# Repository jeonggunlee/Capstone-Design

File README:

[weather Box][raining]
[raining]:https://youtu.be/GDOYBwniNqM

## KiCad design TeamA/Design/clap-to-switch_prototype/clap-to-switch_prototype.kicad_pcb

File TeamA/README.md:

https://github.com/cobaltp/clap-to-switch

Clap-to-Switch Project
Hallym University Capstone Design Project, Spring 2018\
한림대학교 컴퓨터공학과 종합설계프로젝트, 2018년 1학기

Clap-to-Switch Project\
박수 소리로 스위치 작동 프로젝트

목차
==========
1. [개요](#introduction)
1. [알고리즘](#algorithm)
	1. [의사 코드](#pseudocode)
1. [설계](#design)
	1. [회로 설계](#circuit_design)
1. [프로토타입 제작](#prototyping)
	1. [프로토타입 코드](#prototype_code)
	1. [실험 영상](#test_video)
1. [추후 계획](#further_plans)
1. [참조 및 출처](#references)

## 1. 개요<a name='introduction'/>
특정한 박수 패턴(e.g. 337 박수 등)을 이용하여 스위치를 연결하거나 차단시키는 장치를 개발한다.\
마이크를 이용하여 소리를 입력받아 증폭시킨 뒤, 마이크로프로세서의 ADC Input으로 전달하여 패턴을 처리, 기 입력된 패턴과 비교하여 일치할 경우 스위치를 작동 또는 차단시킨다.\
필요할 경우, 패턴 등록 기능 등을 추가한다.

## 2. 작동 알고리즘<a name='algorithm'/>
박수와 음성의 비교\
\

박수 소리와 일반적인 잡음, 음성은 dB가 확연하게 차이나므로 이를 이용하여 마이크로 입력되는 소리에서 박수 소리를 얻어낼 수 있다.\
(단순한 큰 소리와 구분짓는 것은 불가능하지만, 단순한 큰 소리가 패턴으로 나타나는 경우는 없으므로 고려하지 않는다.)

이를 이용하여 알고리즘을 생성할 수 있으며, 다음과 같이 나타낼 수 있다.

변수 목록\
(H), (L): 소리의 최대, 최소 한계치\
(B): 박수 간격\
(C): 박수 측정 간 대기 시간\
(W): 박수 측정 후 대기 시간\
(K): 박수 횟수

1. 입력이 있을 때까지 대기한다.
2. 입력을 확인하여 최대 한계치(H)보다 높을 경우 다음으로 이동, 아닐 경우 1로 이동한다.
3. 만약 타이머가 켜져 있을 경우, 박수 간격 시간(B)을 타이머의 현재 시간으로 설정한 뒤 타이머를 종료한다.
4. (소리가 줄어들 때 까지) 일정 시간(C)동안 대기한다.
5. 입력을 확인하여 최소 한계치(L)보다 낮을 경우 다음으로 이동, 아닐 경우 1로 이동한다.
6. 박수 배열에 박수 간격 시간(B)를 추가하고, 박수 횟수(K)를 1만큼 증가시킨다.
7. 타이머를 초기화한 뒤 다시 시작시킨다.
8. 측정 후 대기시간(W)만큼 대기한다.
9. 장치에 기 입력된 패턴과 사용자가 입력한 박수 패턴을 비교한다.
10. 만약 패턴이 일치할 경우, 스위치를 작동 또는 차단하고, 아닐 경우 1로 이동한다.

### 2.1. 의사 코드<a name='pseudocode'/>
2의 알고리즘을 다음과 같이 Python 스타일의 의사 코드로 작성해보았다.\
(다음 코드는 <a href='https://github.com/cobaltp/Capstone-Design/TeamA/Code/algorithm1.py'>/Code/algorithm1.py</a>의 내용과 동일하다.)

```python3
sensorPin = 5           # 마이크 핀
outputPin = 7           # 출력 핀
thresholdH = 20         # high threshold; Th(H)
thresholdL = 2          # low threshold; Th(L)
tc = 0.05               # clap time; T(c)
tw = 0.1                # 박수간 최소 간격
match = [0, 0.8, 0.4]   # 박수 패턴; clap, 800ms 대기, clap, wait 400ms, clap
clap = []               # 박수 카운터; 값 = 박수간 간격; 100ms 단위로 반올림됨
tb = 0                  # 박수간 간격
timeout = Timer(2, callback())  # 타임아웃 타이머; 타이머 완료 시 박수 카운터 초기화
 
def callback():
    del clap[:]         # 타이머 완료 시 박수 카운터 초기화
 
def loop():
    if read(sensorPin) > thresholdH:                # 값이 최대값보다 높은 지 확인
        if timeout.isEnabled():                     # 타이머가 켜져 있을 경우
            tb = round(timeout.getInterval(), 1)    # 소수점 1번째 자리까지 반올림
            timeout.Stop()                          # 타이머 멈춤
        sleep(tc)                                   # T(c) 동안 대기
        if read(sensorPin) < thresholdL:            # 값이 최소값보다 낮은 지 확인
            clap.append(tb)                         # 박수 카운터에 박수간 간격 추가
            timeout.start()                         # 타이머 시작
    if match == clap:                               # 패턴과 입력 값이 일치할 경우
        write(outputPin, write(outputPin))          # 출력 핀을 작동한다
```

## 3. 설계<a name='design'/>
장치를 구성하기 위해 필요한 회로는 다음과 같다.

1. 오디오 증폭 회로
2. 마이크로프로세서 회로
3. (필요할 경우) 전원 회로

### 3.1. 회로 설계<a name='circuit_design'/>
무료 EDA 툴인 <a href='http://http://kicad-pcb.org/'>KiCad</a>를 이용하여 다음과 같이 회로 도면을 작성하였다.\
KiCad용 회로 파일은 <a href='https://github.com/cobaltp/Capstone-Design/TeamA/Design/clap-to-switch_prototype/'>/Design/clap-to-switch_prototype</a>에서 구할 수 있다.\
부품 상세 내용은 <a href='https://github.com/cobaltp/Capstone-Design/blob/master/TeamA/예산%20계획서'>예산 계획서 파일</a>을 참조하라.

\
전체 회로의 모습.

각 회로를 확대하면 다음과 같다.

\
오디오 증폭 회로

\
마이크로프로세서 회로

\
전원 회로(9V-5V 레귤레이터 회로)

## 4. 프로토타입 제작<a name='prototyping'/>
ATTiny를 이용하여 프로토타입을 제작하였다.\
(ATTiny로의 업로드는 Arduino를 ISP로 사용하여 진행하였다. 다음 링크를 참조하였다.)\
(https://kocoafab.cc/tutorial/view/289)

회로 세부 부분 설명

## 4.1. 프로토타입 코드<a name='prototype_code'/>
프로토타입에 사용한 코드는 다음과 같다.\
(<a href='https://github.com/cobaltp/Capstone_Design/TeamA/Code/cts_03/cts_03.ino'>/Code/cts_03/cts_03.ino</a>)

```cpp
#include "TimerObject.h"
#include "SoftwareServo.h"

// pin variables
int buttonPin = 2;
int r_ledPin = 4;
int g_ledPin = 0;
int servoPin = 1;
int micPin = 3;

SoftwareServo servo;            // 서보
int servoStatus = 0;            // 서보 상태
TimerObject *timeout;           // 타이머
int onRecord = 0;               // 기록 상태
int thresholdH = 600;           // high threshold; Th(H)
int thresholdL = 550;           // low threshold; Th(L)
int tc = 50;                    // clap sound wave time; T(c)
int tw = 100;                   // 대기 시간; T(w)
int tr = 200;                   // 박수 간격; T(r)
int match[10] = {0, 800, 200};  // 박수 패턴; clap, 800ms 대기, clap, 400ms 대기, clap
int ml = 3;                     // 패턴 길이
int claps[10] = {0};            // 박수 입력
int cc = 0;                     // 입력 박수 횟수
int tb = 0;                     // 박수 간 간격(ms)

void setup() {
    servo.attach(servoPin);
    moveServo();
    
    pinMode(buttonPin, INPUT_PULLUP);
    pinMode(r_ledPin, OUTPUT);                      // 핀 모드 설정; LED핀, 출력
    pinMode(g_ledPin, OUTPUT);                      // 핀 모드 설정; LED핀, 출력

    timeout = new TimerObject(2000, &callback);     // 타이머 생성; 2초
}

void led_blink(int ledPin, int count) {
    for (int i = 0; i < count; i++) {
        digitalWrite(ledPin, HIGH);
        delay(100);
        digitalWrite(ledPin, LOW);
        delay(100);
    }
}

void callback() {                            // 초기화 함수; 타이머 시간 도달 시 발생
    if (onRecord){
        memcpy(match, claps, 10);
        onRecord = 0;
        led_blink(r_ledPin, 3);
        // Serial.println("new pattern set");
    }
    
    memset(claps, 0, sizeof(int) * 10);
    cc = 0;
    tb = 0;
    timeout->Stop();
    led_blink(g_ledPin, 3);
}

int round_t(int t, int v) {                 // 정수 반올림 함수
    return (int)(round((float)t / v) * v);
}

bool checkMatch(int *match, int *claps) {   // 패턴 검사
    for (int i = 0; i < 10; i++) {
        if (match[i] != claps[i])
            return false;
    }
    return true;
}

void moveServo() {
    if (servoStatus == 0)  { servo.write(80); servoStatus = 1; }
    else                   { servo.write(10); servoStatus = 0; }
}

void loop() {
    if (digitalRead(buttonPin) == HIGH && onRecord == 0) {
        onRecord = 1;
        led_blink(r_ledPin, 5);
        digitalWrite(r_ledPin, HIGH);
    }
      
    if (analogRead(micPin) > thresholdH) {
        if (timeout->isEnabled()) {
            tb = round_t(timeout->getCurrentTime(), 200);
            timeout->Stop();  
        }
        delay(tc);
        if (analogRead(micPin) < thresholdL) {
            claps[cc++] = tb;
            printArray(claps);
            timeout->Start();
            digitalWrite(g_ledPin, HIGH);
            delay(tw);
            digitalWrite(g_ledPin, LOW);
        }
    }
    
    if (checkMatch(match, claps) && onRecord == 0) {
        moveServo();
        digitalWrite(r_ledPin, HIGH);
        delay(500);
        digitalWrite(r_ledPin, LOW);
        callback();
    }
    
    SoftwareServo::refresh();
    timeout->Update();
}
```

### 4.2. 실험 영상<a name='test_video'/>
]

박수를 인식하면 녹색 LED가 점멸하며, 특정 패턴을 입력하여 인식에 성공한 경우 일정 시간 동안 붉은색 LED가 점등한다.

## 5. 추후 계획<a name='further_plans'/>
프로토타입 방식으로 제작한 현재 장치를 브래드보드를 이용하여 실물로 제작하는 게 우선이다.\
그 다음으로는 입출력의 확대가 있겠다.\
현재는 출력 장치가 1개뿐이 없지만, 추후 인식할 수 있는 패턴을 여러 개로 늘리고 출력을 확장하여 활용성을 높혀야 한다.\
(입출력 핀이 많은 마이크로컨트롤러를 사용하거나, 시프트 레지스터를 이용할 수 있겠다.)

## 6. 출처 및 참조<a name='references'/>
YouTube - Turn your lights on with clapping?! by GreatScott!! (https://www.youtube.com/watch?v=7Ao6KD8f9J4) \
LM386 microphone amplifier by Dimitar Kovachev (https://lowvoltage.wordpress.com/2011/05/15/lm386-mic-amp/) \
LM386 Power Amplifier Datasheet by Texas Instruments (http://www.ti.com/lit/ds/symlink/lm386.pdf)

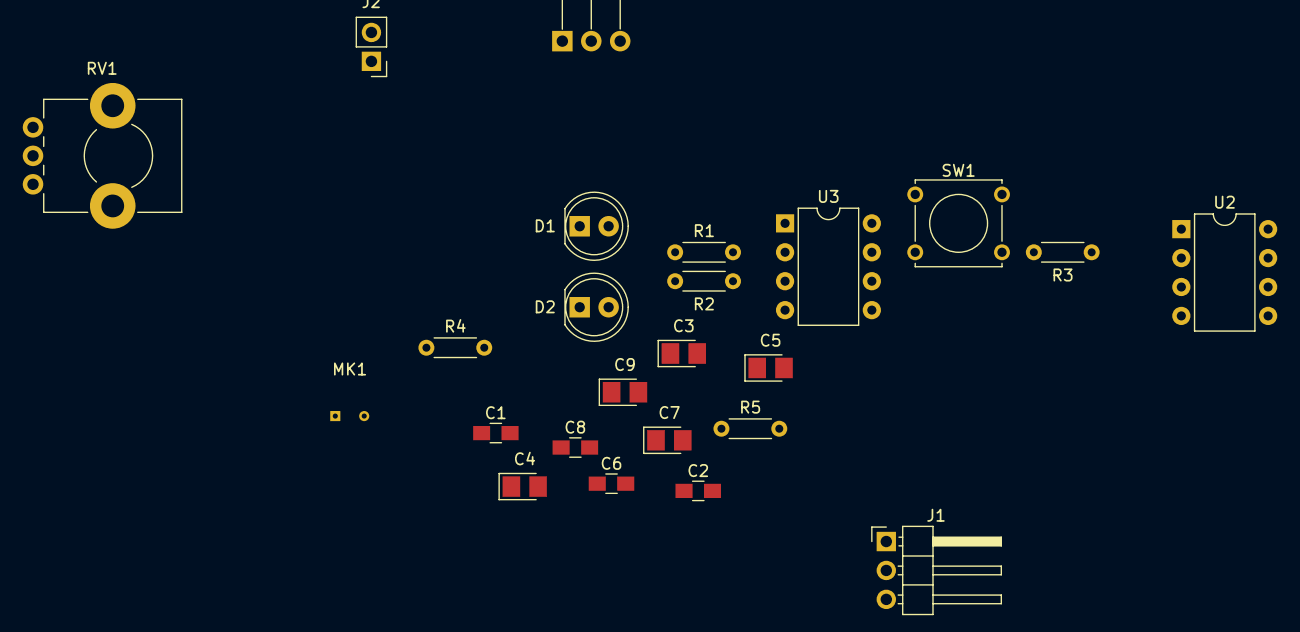
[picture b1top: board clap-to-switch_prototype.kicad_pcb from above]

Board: 2 copper layers, 24 parts (0 on the bottom side), 18 nets, no tracks yet.

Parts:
C1: 330nF; C_0805_HandSoldering
C2, C8: 100nF; C_0805_HandSoldering
C3, C4, C5: 10uF; CP_Tantalum_Case-R_EIA-2012-12_Reflow
C6: 47nF; C_0805_HandSoldering
C7: 220uF; CP_Tantalum_Case-R_EIA-2012-12_Reflow
C9: 100uF; CP_Tantalum_Case-R_EIA-2012-12_Reflow
D1: LED_G; LED_D5.0mm
D2: LED_R; LED_D5.0mm
J1: CServ; Pin_Header_Angled_1x03_Pitch2.54mm
J2: CBat; Pin_Header_Straight_1x02_Pitch2.54mm
MK1: Mic; CMA-4544PF-W
R1: 100; R_Axial_DIN0204_L3.6mm_D1.6mm_P5.08mm_Horizontal
R2: 180; R_Axial_DIN0204_L3.6mm_D1.6mm_P5.08mm_Horizontal
R3: 10K; R_Axial_DIN0204_L3.6mm_D1.6mm_P5.08mm_Horizontal
R4: 4.7K; R_Axial_DIN0204_L3.6mm_D1.6mm_P5.08mm_Horizontal
R5: 10; R_Axial_DIN0204_L3.6mm_D1.6mm_P5.08mm_Horizontal
RV1: POT; Potentiometer_Alps_RK09K_Horizontal
SW1: SW; SW_Tactile_Straight_KSA0Axx1LFTR
U1: L7805; TO-220-3_Horizontal
U2: LM386; DIP-8_W7.62mm
U3: ATTINY85-20PU; DIP-8_W7.62mm

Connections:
+5V: C2.1, C8.1, C9.1, J1.2, R4.1, SW1.2, U1.3, U2.6, U3.8
/AUD_UC: C6.1, C7.1, U2.5, U3.5
/SERVO: J1.3, U3.6
GND: C1.2, C2.2, C4.1, C8.2, C9.2, D1.1, D2.1, J1.1, J2.1, MK1.1, R3.2, R5.2, RV1.3, SW1.1, U1.2, U2.2, U2.4, U3.4
unnamed: C1.1, J2.2, U1.1
unnamed: C3.1, MK1.2, R4.2
unnamed: C3.2, RV1.1
unnamed: C4.2, U2.7
unnamed: C5.1, U2.1
unnamed: C5.2, U2.8
unnamed: C6.2, R5.1
unnamed: D1.2, R1.1
unnamed: D2.2, R2.1
unnamed: R1.2, U3.2
unnamed: R2.2, U3.3
unnamed: R3.1, SW1.3
unnamed: RV1.2, U2.3
unnamed: SW1.4, U3.7

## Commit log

2018-03-12 Add files via upload
    발표자료 2주차 입니다.
2018-03-18 Add files via upload
    계획발표 자료 업로드
2018-03-20 README.md is modified
2018-03-25 kkkk조 4주차 발표자료 업로드입니다.
    이번주에는
    서보모터를 활용한 차단기 실습.
    초음파센서와 서보모터를 활용한 일정 거리 시 차단기 작동 유무
    블루투스모듈 실습
    을 진행하였습니다.
2018-03-26 week4.ppt
2018-03-26 week1, week2, week3 발표자료
2018-03-26 업로드 테스트입니다.
    업로드 테스트입니다.
2018-03-26 새 폴더 생성 및 업로드
    발표 자료 폴더 생성 및 발표 자료 업로드했습니다.
2018-03-31 Add files via upload
    kkkk조 5주차 발표자료입니다.
    이번주에 진행한 내용은 2개의 서로 다른 블루투스 모듈로
    양방향 데이터통신을 진행하였습니다.
    블루투스가 서로 연결되면 서보모터가 작동하게 실습해봤습니다.
2018-04-02 week5 발표자료입니다
2018-04-08 0409 발표자료 업로드
2018-04-08 0408 자료 업데이트
    발표자료, 실험 이미지, 예산 계획서, 코드 등
2018-04-08 종합설계프로젝트 ppt 입니다.
    종합설계프로젝트 ppt 입니다.
2018-04-08 6주차 발표자료입니다.
    6주차에는 웹서버 및 영상처리를 위한 기초 단계 수립과
    차연산을 통한 물체감지 코드를 변형 및 실행시켜 보았습니다
2018-04-09 week6 발표자료 입니다
2018-04-24 Add files via upload
    아두이노 블루투스에 필요한 AT신호보내는것을 해결하였고,
    openCV를 RGB값을 이용하여 흰색값을 검출하려하였으나 실패함.(다른 방안 모색중)
    시리얼 통신을 통한 아두이노와 라즈베리파이간의 통신을 공부함.(아두이노의 값을 웹서버에 올리기 위함)
2018-04-24 0425 자료 업데이트
    발표자료 및 코드
2018-04-29 20180430 자료 업데이트
    발표자료 및 코드 업데이트
2018-05-08 9주차 발표자료입니다.
    OPENCV 탬플릿매칭과 Haarcascade학습을 진행하였고
    아두이노 비콘 생성과 비콘 스캐너를 이용하여 UUID와 거리값을 확인하였습니다.
2018-05-08 0509 자료 업데이트
    발표자료, 코드(cts_02), 이미지 추가
2018-05-20 12주차 발표자료입니다.
    opencv 탬플릿매칭과 제누이노 101과 비콘과의 연결과 초음파 센서 및 서보모터, 데이터베이스 구현을 진행하여 가상 주차장을 구현해보았습니다.
2018-05-29 0530 코드 업데이트
    코드 업데이트
2018-05-29 0530 발표자료 및 디자인 업로드
    발표 자료, EDA 디자인 업로드
    cts_03 코드 일부 수정
2018-06-04 ppt 정리
2018-06-23 Rename WeatherBox to README
2018-06-23 Rename README.md to README_1.md
2018-06-23 최종발표_ppt
2018-06-24 README.md
    final update
2018-06-24 FINAL FINAL
2018-06-25 0625 최종 결과보고
2018-06-25 0625 결과 발표 업데이트
    결과보고 작성, 이미지 업로드, 파일명 정리 등
2018-06-25 0625 결과발표 업데이트
    결과문 작성, 이미지 등록, 파일명 정리 등
2018-06-25 0625 최종 발표 업데이트
2018-06-25 0625 결과 발표 업데이트
